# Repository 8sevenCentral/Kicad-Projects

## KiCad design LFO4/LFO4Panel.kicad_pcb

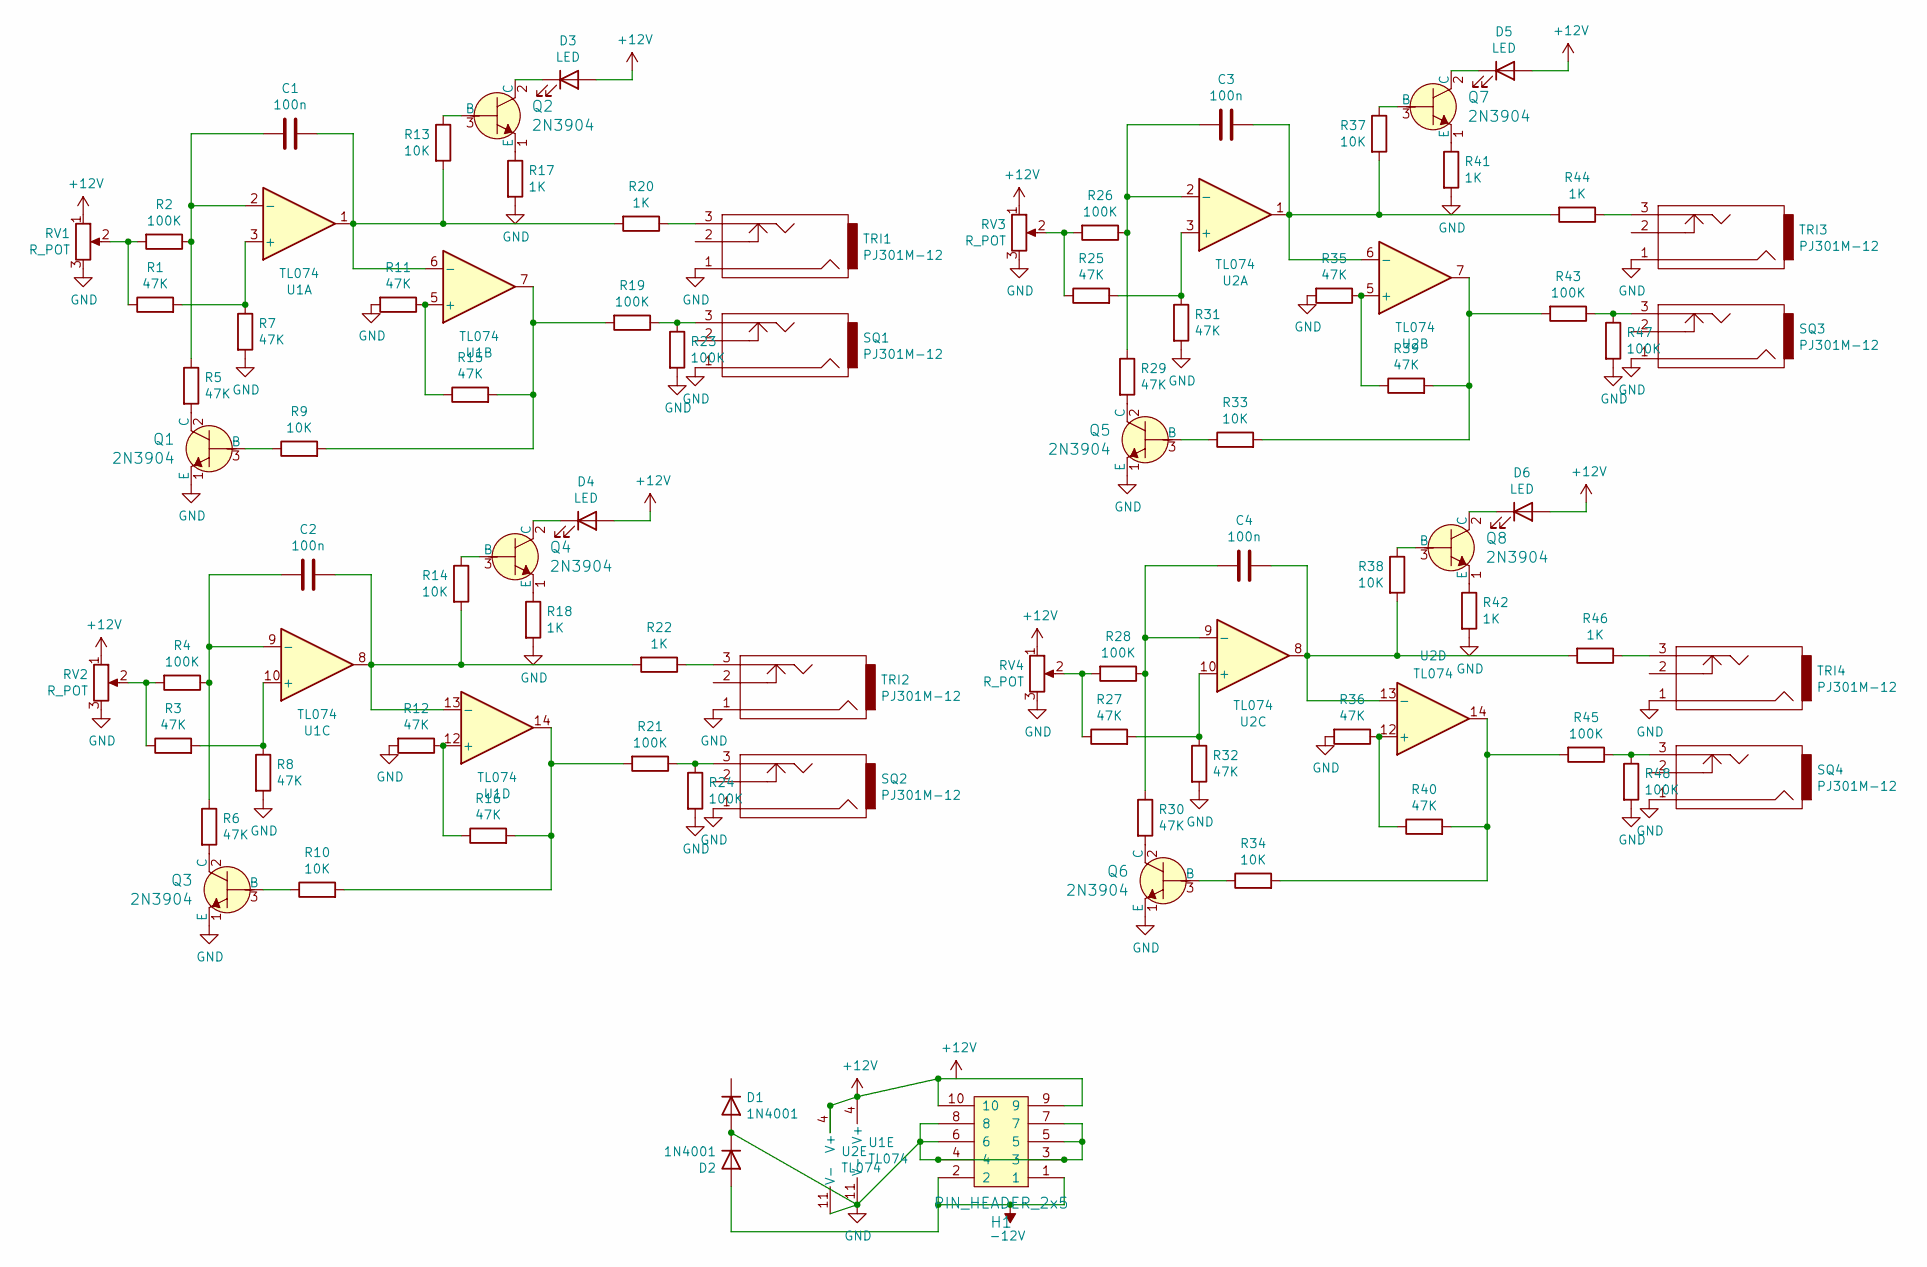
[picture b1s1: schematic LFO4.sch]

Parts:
C1, C2, C3, C4: 100n; C_0805_HandSoldering
D1, D2: 1N4001; D_0805
D3, D4, D5, D6: LED; LED3mm
H1: PIN_HEADER_2x5; Pin_Header_Straight_2x05_Pitch2.54mm
Q1, Q2, Q3, Q4, Q5, Q6, Q7, Q8: 2N3904; SOT-23_Handsoldering; MPN 2N3904; Digi-Key_PN 2N3904CS-ND
R1, R3, R5, R6, R7, R8, R11, R12, R15, R16, R25, R27, R29, R30, R31, R32, R35, R36, R39, R40: 47K; R_0805_HandSoldering
R2, R4, R19, R21, R23, R24, R26, R28, R43, R45, R47, R48: 100K; R_0805_HandSoldering
R9, R10, R13, R14, R33, R34, R37, R38: 10K; R_0805_HandSoldering
R17, R18, R20, R22, R41, R42, R44, R46: 1K; R_0805_HandSoldering
RV1, RV2, RV3, RV4: R_POT; Alpha9mmPot
SQ1, SQ2, SQ3, SQ4: PJ301M-12
TRI1, TRI2, TRI3, TRI4: PJ301M-12
U1, U2: TL074; SOIC-14_3.9x8.7mm_Pitch1.27mm

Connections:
+12V: D3.2 (A), D4.2 (A), D5.2 (A), D6.2 (A), H1.9, H1.10, RV1.1, RV2.1, RV3.1, RV4.1, U1.4 (V+), U2.4 (V+)
-12V: D2.2 (A), H1.1, H1.2
GND: D1.2 (A), D2.1 (K), H1.3, H1.4, H1.5, H1.6, H1.7, H1.8, Q1.1 (E), Q3.1 (E), Q5.1 (E), Q6.1 (E), R7.2, R8.2, R11.2, R12.2, R17.2, R18.2, R23.2, R24.2, R31.2, R32.2, R35.2, R36.2, R41.2, R42.2, R47.2, R48.2, RV1.3, RV2.3, RV3.3, RV4.3, SQ1.1, SQ2.1, SQ3.1, SQ4.1, TRI1.1, TRI2.1, TRI3.1, TRI4.1, U1.11 (V-), U2.11 (V-)
unnamed: C1.1, R13.2, R20.2, U1.1, U1.6 (-)
unnamed: C1.2, R2.1, R5.1, U1.2 (-)
unnamed: C2.1, R14.2, R22.2, U1.8, U1.13 (-)
unnamed: C2.2, R4.1, R6.1, U1.9 (-)
unnamed: C3.1, R37.2, R44.2, U2.1, U2.6 (-)
unnamed: C3.2, R26.1, R29.1, U2.2 (-)
unnamed: C4.1, R38.2, R46.2, U2.8, U2.13 (-)
unnamed: C4.2, R28.1, R30.1, U2.9 (-)
unnamed: D3.1 (K), Q2.2 (C)
unnamed: D4.1 (K), Q4.2 (C)
unnamed: D5.1 (K), Q7.2 (C)
unnamed: D6.1 (K), Q8.2 (C)
unnamed: Q1.2 (C), R5.2
unnamed: Q1.3 (B), R9.1
unnamed: Q2.1 (E), R17.1
unnamed: Q2.3 (B), R13.1
unnamed: Q3.2 (C), R6.2
unnamed: Q3.3 (B), R10.1
unnamed: Q4.1 (E), R18.1
unnamed: Q4.3 (B), R14.1
unnamed: Q5.2 (C), R29.2
unnamed: Q5.3 (B), R33.1
unnamed: Q6.2 (C), R30.2
unnamed: Q6.3 (B), R34.1
unnamed: Q7.1 (E), R41.1
unnamed: Q7.3 (B), R37.1
unnamed: Q8.1 (E), R42.1
unnamed: Q8.3 (B), R38.1
unnamed: R1.1, R2.2, RV1.2
unnamed: R1.2, R7.1, U1.3 (+)
unnamed: R3.1, R4.2, RV2.2
unnamed: R3.2, R8.1, U1.10 (+)
unnamed: R10.2, R16.2, R21.2, U1.14
unnamed: R11.1, R15.1, U1.5 (+)
unnamed: R12.1, R16.1, U1.12 (+)
unnamed: R9.2, R15.2, R19.2, U1.7
unnamed: R19.1, R23.1, SQ1.3
unnamed: R20.1, TRI1.3
unnamed: R21.1, R24.1, SQ2.3
unnamed: R22.1, TRI2.3
unnamed: R25.1, R26.2, RV3.2
unnamed: R25.2, R31.1, U2.3 (+)
unnamed: R27.1, R28.2, RV4.2
unnamed: R27.2, R32.1, U2.10 (+)
unnamed: R33.2, R39.2, R43.2, U2.7
unnamed: R34.2, R40.2, R45.2, U2.14
unnamed: R35.1, R39.1, U2.5 (+)
unnamed: R36.1, R40.1, U2.12 (+)
unnamed: R43.1, R47.1, SQ3.3
unnamed: R44.1, TRI3.3
unnamed: R45.1, R48.1, SQ4.3
unnamed: R46.1, TRI4.3

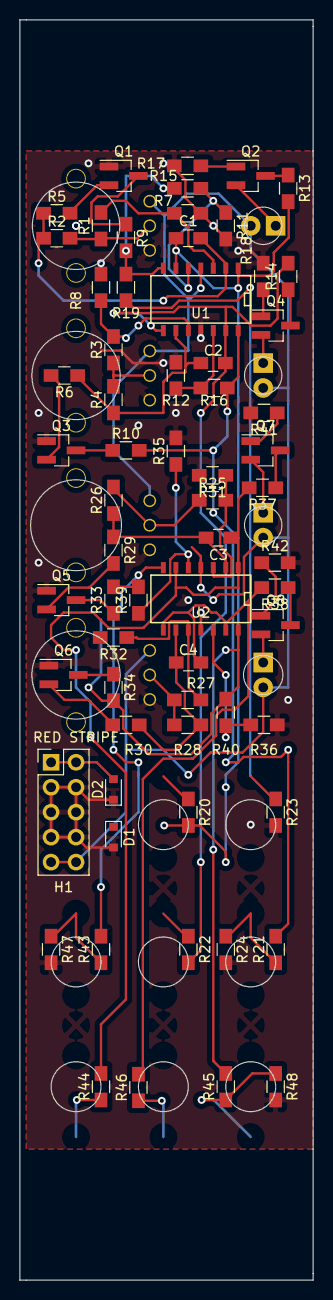
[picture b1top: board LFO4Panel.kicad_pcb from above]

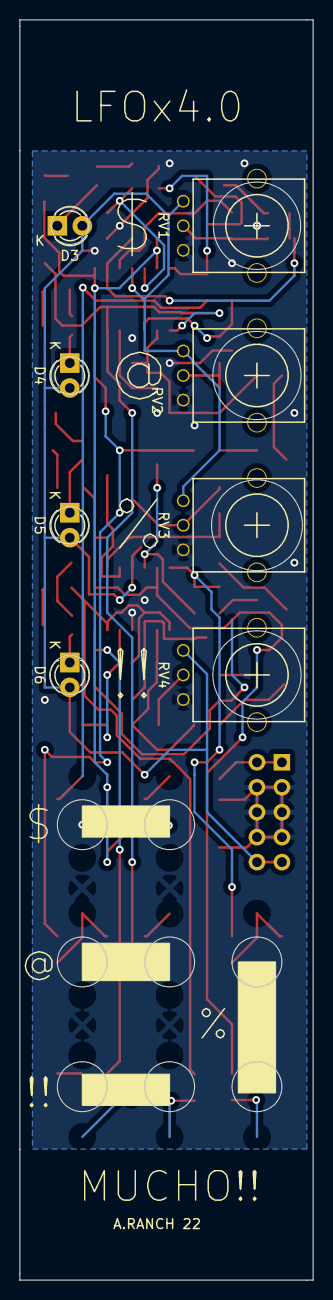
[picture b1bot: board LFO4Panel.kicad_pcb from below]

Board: 2 copper layers, 29.8 x 128.3 mm, 73 parts (8 on the bottom side), 51 nets.
